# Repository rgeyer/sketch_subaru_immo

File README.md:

# Sketch Subaru IMMO
Assets for PCBs, and arduino sketch(es) relating to hacking my 2005 Subaru Outback XT engine computer.

## EAGLE
The `eagle` directory contains the PCBs. Including the following.

1. `immo_programmer` - A (reasonbly mature) immobilizer EEPROM programming tool.
2. `Bench` - A PCB which is designed to allow bench testing of the ECU/BIU/CM, which breaks out key signals (CANbus, IMMO serial, security light, etc), and includes a Teensy 3.5/3.6 for reading and manipulating singnals.
3. `ArduinoLogger` - A VERY incomplete prototype for logging CANbus, SSM, and immobilizer signals. Meant as a one-stop-shop for all data logging. Still needs lots of work.

## Sketches
There is really only one sketch, which is in the root of the repo currently. It's the arduino firmware for the `immo_programmer` board. It is meant to be interfaced by the [93l56r-cli](https://github.com/rgeyer/93l56r-cli/) golang app to read/write the EEPROMs related to the immobilizer system.

## Fritzing diagrams
The `fritzing` directory includes visual diagrams for the wiring schematics on breadboards, for those who may not be using my manufactured PCB.

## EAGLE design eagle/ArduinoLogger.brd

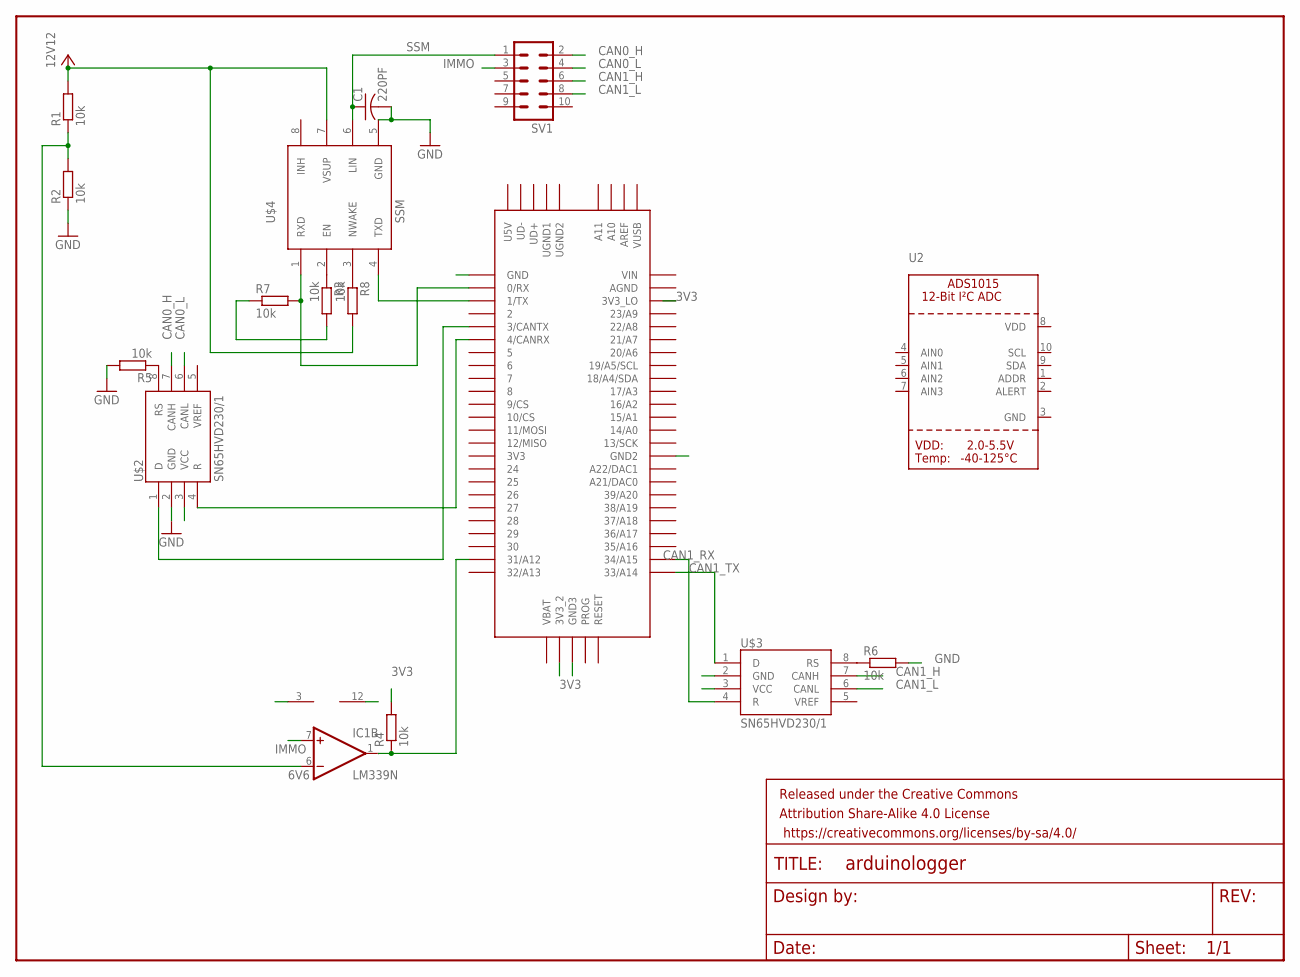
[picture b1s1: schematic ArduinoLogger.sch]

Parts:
C1: 220PF; C050-024X044
FRAME1: FRAME-LETTER; CREATIVE_COMMONS
IC1: LM339N; DIL14
R1, R2, R3, R4, R5, R6, R7, R8: 10k; 0204/7
SV1: MA05-2
U2: ADC_ADS1015; MSOP10
U$1: TEENSY_3.5/3.6
U$2, U$3: SN65HVD230/1; SO8
U$4: SSM; SOIC8

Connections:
3V3: R3.2, R4.2, R7.1, U$1.3V3_2, U$1.3V3_LO, U$2.3 (VCC), U$3.3 (VCC)
6V6: IC1.6 (-IN), R1.1, R2.2
+12V: IC1.3 (V+), R1.2, R8.2, U$4.7 (VSUP)
CAN0_H: SV1.2, U$2.7 (CANH)
CAN0_L: SV1.4, U$2.6 (CANL)
CAN1_H: SV1.6, U$3.7 (CANH)
CAN1_L: SV1.8, U$3.6 (CANL)
CAN1_RX: U$1.34/A15, U$3.4 (R)
CAN1_TX: U$1.33/A14, U$3.1 (D)
GND: C1.2, IC1.12 (GND), R2.1, R5.2, R6.2, U$1.GND, U$1.GND2, U$1.GND3, U$2.2 (GND), U$3.2 (GND), U$4.5 (GND)
IMMO: IC1.7 (+IN), SV1.3
unnamed: U$1.3/CANTX, U$2.1 (D)
unnamed: IC1.1 (OUT), R4.1, U$1.31/A12
unnamed: R7.2, U$1.0/RX, U$4.1 (RXD)
unnamed: R3.1, U$4.2 (EN)
unnamed: R8.1, U$4.3 (NWAKE)
unnamed: U$1.4/CANRX, U$2.4 (R)
unnamed: R5.1, U$2.8 (RS)
unnamed: R6.1, U$3.8 (RS)
unnamed: U$1.1/TX, U$4.4 (TXD)
SSM: C1.1, SV1.1, U$4.6 (LIN)

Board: 2 copper layers, 17 parts (0 on the bottom side), 21 nets, no tracks yet.

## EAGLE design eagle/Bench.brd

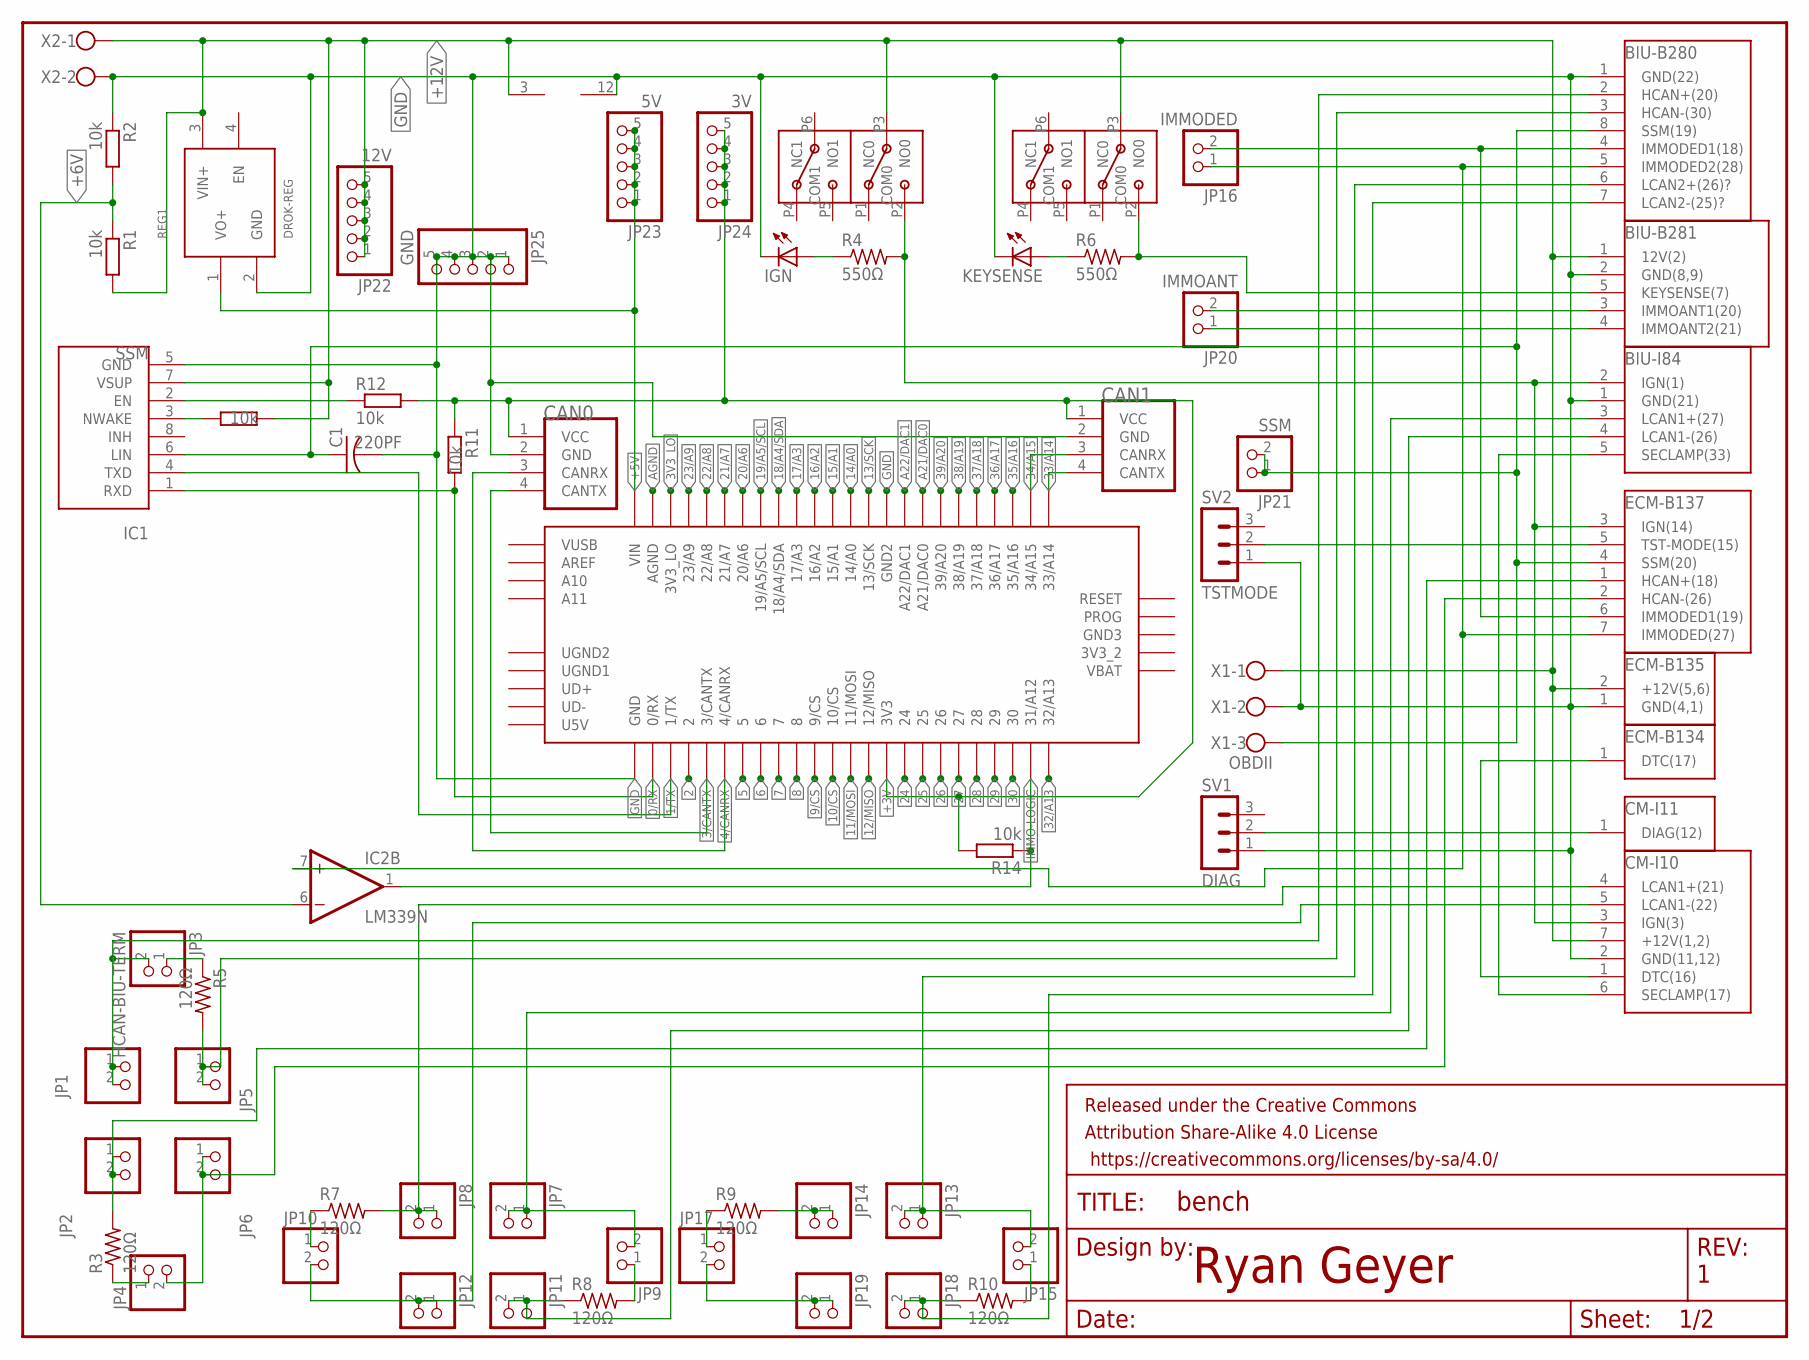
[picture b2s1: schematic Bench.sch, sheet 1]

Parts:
C1: 220PF; C050-024X044
CAN0, CAN1: SN65HVD230D-BREAKOUT; 1X04
CONN1: CM-110
CONN2: CM-I11; ECM-B134
CONN3: BIU-B280
CONN4: BIU-B281
CONN5: BIU-I84
CONN6: ECM-B135
CONN7: ECM-B137
CONN8: ECM-B134
FRAME1: FRAME-LETTER; CREATIVE_COMMONS
IC1: SSM; DIL8
IC2: LM339N; DIL14
IGN: LED3MM
JP1, JP2, JP4, JP5, JP6, JP7, JP8, JP9, JP10, JP11, JP12, JP13, JP14, JP15, JP17, JP18, JP19: PINHD-1X2; 1X02
JP3: HCAN-BIU-TERM; 1X02
JP16: IMMODED; 1X02
JP20: IMMOANT; 1X02
JP21: SSM; 1X02
JP22: 12V; 1X05
JP23: 5V; 1X05
JP24: 3V; 1X05
JP25: GND; 1X05
KEYSENSE: LED3MM
MCU1: TEENSY_3.5/3.6
R1, R2, R11, R12, R13, R14: 10k; 0207/10
R3, R5, R7, R8, R9, R10: 120Ω; 0207/10
R4, R6: 550Ω; 0207/10
REG1: DROK-REG
SV1: DIAG; MA03-1
SV2: TSTMODE; MA03-1
SW1, SW2: 8MM-DPDT
X1: OBDII; W237-103
X2: GND; W237-102

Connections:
0/RX: IC1.1 (RXD), MCU1.0/RX, R11.2; also elsewhere on the board
1/TX: IC1.4 (TXD), MCU1.1/TX; also elsewhere on the board
2: MCU1.2; also elsewhere on the board
3/CANTX: CAN0.4 (CANTX), MCU1.3/CANTX; also elsewhere on the board
3V3_LO: MCU1.3V3_LO; also elsewhere on the board
4/CANRX: CAN0.3 (CANRX), MCU1.4/CANRX; also elsewhere on the board
5: MCU1.5; also elsewhere on the board
6: MCU1.6; also elsewhere on the board
7: MCU1.7; also elsewhere on the board
8: MCU1.8; also elsewhere on the board
9/CS: MCU1.9/CS; also elsewhere on the board
10/CS: MCU1.10/CS; also elsewhere on the board
11/MOSI: MCU1.11/MOSI; also elsewhere on the board
12/MISO: MCU1.12/MISO; also elsewhere on the board
13/SCK: MCU1.13/SCK; also elsewhere on the board
14/A0: MCU1.14/A0; also elsewhere on the board
15/A1: MCU1.15/A1; also elsewhere on the board
16/A2: MCU1.16/A2; also elsewhere on the board
17/A3: MCU1.17/A3; also elsewhere on the board
18/A4/SDA: MCU1.18/A4/SDA; also elsewhere on the board
19/A5/SCL: MCU1.19/A5/SCL; also elsewhere on the board
20/A6: MCU1.20/A6; also elsewhere on the board
21/A7: MCU1.21/A7; also elsewhere on the board
22/A8: MCU1.22/A8; also elsewhere on the board
23/A9: MCU1.23/A9; also elsewhere on the board
24: MCU1.24; also elsewhere on the board
25: MCU1.25; also elsewhere on the board
26: MCU1.26; also elsewhere on the board
27: MCU1.27; also elsewhere on the board
28: MCU1.28; also elsewhere on the board
29: MCU1.29; also elsewhere on the board
30: MCU1.30; also elsewhere on the board
32/A13: MCU1.32/A13; also elsewhere on the board
33/A14: CAN1.4 (CANTX), MCU1.33/A14; also elsewhere on the board
34/A15: CAN1.3 (CANRX), MCU1.34/A15; also elsewhere on the board
35/A16: MCU1.35/A16; also elsewhere on the board
36/A17: MCU1.36/A17; also elsewhere on the board
37/A18: MCU1.37/A18; also elsewhere on the board
38/A19: MCU1.38/A19; also elsewhere on the board
39/A20: MCU1.39/A20; also elsewhere on the board
+3V: CAN0.1 (VCC), CAN1.1 (VCC), JP24.1, JP24.2, JP24.3, JP24.4, JP24.5, MCU1.3V3, R11.1, R12.2, R14.2; also elsewhere on the board
+5V: JP23.1, JP23.2, JP23.3, JP23.4, JP23.5, MCU1.VIN, REG1.1 (VO+); also elsewhere on the board
+6V: IC2.6 (-IN), R1.1, R2.2
+12V: CONN1.7 (+12V(1,2)), CONN4.1 (12V(2)), CONN6.2 (+12V(5,6)), IC1.7 (VSUP), IC2.3 (V+), JP22.1, JP22.2, JP22.3, JP22.4, JP22.5, R1.2, R13.2, REG1.3 (VIN+), SW1.P3 (COM0), SW2.P3 (COM0), X1.1, X2.1
A21/DAC0: MCU1.21/DAC0 (A21/DAC0); also elsewhere on the board
A22/DAC1: MCU1.A22/DAC1; also elsewhere on the board
AGND: MCU1.AGND; also elsewhere on the board
GND: C1.2, CAN0.2 (GND), CAN1.2 (GND), CONN1.2 (GND(11,12)), CONN3.1 (GND(22)), CONN4.2 (GND(8,9)), CONN5.1 (GND(21)), CONN6.1 (GND(4,1)), IC1.5 (GND), IC2.12 (GND), IGN.K (C), JP25.1, JP25.2, JP25.3, JP25.4, JP25.5, KEYSENSE.K (C), MCU1.GND, MCU1.GND2, R2.1, REG1.2 (GND), SV1.1, SV2.1, X1.2, X2.2; also elsewhere on the board
HCAN+(BIU): CONN3.2 (HCAN+(20)), JP1.1, JP1.2, JP3.2
HCAN+(ECM): CONN7.1 (HCAN+(18)), JP2.1, JP2.2, R3.2
HCAN-(BIU): CONN3.3 (HCAN-(30)), JP5.1, JP5.2, R5.2
HCAN-(ECM): CONN7.2 (HCAN-(26)), JP4.2, JP6.1, JP6.2
IGN: CONN1.3 (IGN(3)), CONN5.2 (IGN(1)), CONN7.3 (IGN(14)), R4.2, SW1.P2 (NO0)
IMMO-LOGIC: IC2.1 (OUT), MCU1.31/A12, R14.1; also elsewhere on the board
KEYSENSE: CONN4.5 (KEYSENSE(7)), R6.2, SW2.P2 (NO0)
LCAN1+(BIU): CONN5.3 (LCAN1+(27)), JP7.1, JP7.2, JP9.2
LCAN1+(CM): CONN1.4 (LCAN1+(21)), JP8.1, JP8.2, R7.2
LCAN1-(BIU): CONN5.4 (LCAN1-(26)), JP11.1, JP11.2, R8.1
LCAN1-(CM): CONN1.5 (LCAN1-(22)), JP10.2, JP12.1, JP12.2
LCAN2+(BIU): CONN3.6 (LCAN2+(26)?), JP13.1, JP13.2, JP15.2
LCAN2+(CLI): JP14.1, JP14.2, R9.2
LCAN2-(BIU): CONN3.7 (LCAN2-(25)?), JP18.1, JP18.2, R10.1
LCAN2-(CLI): JP17.2, JP19.1, JP19.2
unnamed: IGN.A, R4.1
unnamed: CONN1.6 (SECLAMP(17)), CONN5.5 (SECLAMP(33))
unnamed: KEYSENSE.A, R6.1
unnamed: CONN1.1 (DTC(16)), CONN8.1
unnamed: CONN2.1, SV1.2
unnamed: JP9.1, R8.2
unnamed: JP3.1, R5.1
unnamed: JP4.1, R3.1
unnamed: JP10.1, R7.1
unnamed: JP15.1, R10.2
unnamed: IC1.2 (EN), R12.1
unnamed: IC1.3 (NWAKE), R13.1
unnamed: JP17.1, R9.1
unnamed: CONN3.4 (IMMODED1(18)), CONN7.6 (IMMODED1(19)), JP16.2
unnamed: CONN3.5 (IMMODED2(28)), CONN7.7 (IMMODED(27)), IC2.7 (+IN), JP16.1
unnamed: CONN4.3 (IMMOANT1(20)), JP20.2
unnamed: CONN4.4 (IMMOANT2(21)), JP20.1
SSM: C1.1, CONN3.8 (SSM(19)), CONN7.4 (SSM(20)), IC1.6 (LIN), JP21.1, JP21.2, X1.3
TSTMODE: CONN7.5 (TST-MODE(15)), SV2.2

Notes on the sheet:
Ryan Geyer

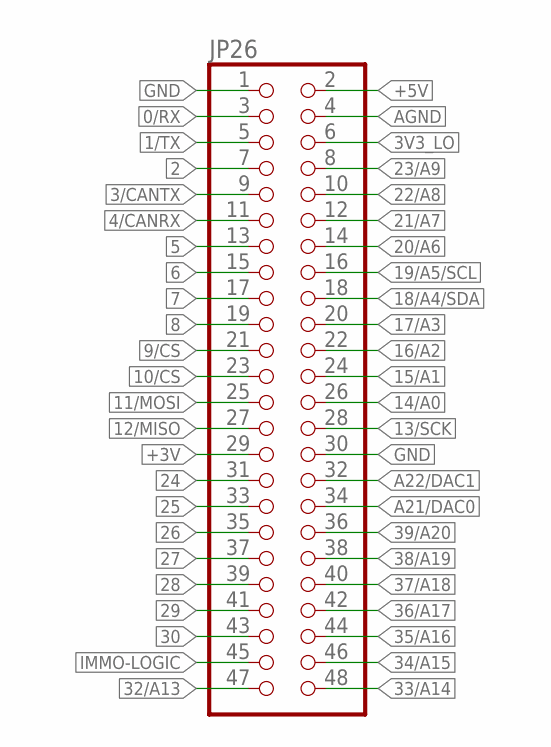
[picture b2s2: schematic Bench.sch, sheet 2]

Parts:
JP26: PINHD-2X24; 2X24

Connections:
0/RX: JP26.3; also elsewhere on the board
1/TX: JP26.5; also elsewhere on the board
2: JP26.7; also elsewhere on the board
3/CANTX: JP26.9; also elsewhere on the board
3V3_LO: JP26.6; also elsewhere on the board
4/CANRX: JP26.11; also elsewhere on the board
5: JP26.13; also elsewhere on the board
6: JP26.15; also elsewhere on the board
7: JP26.17; also elsewhere on the board
8: JP26.19; also elsewhere on the board
9/CS: JP26.21; also elsewhere on the board
10/CS: JP26.23; also elsewhere on the board
11/MOSI: JP26.25; also elsewhere on the board
12/MISO: JP26.27; also elsewhere on the board
13/SCK: JP26.28; also elsewhere on the board
14/A0: JP26.26; also elsewhere on the board
15/A1: JP26.24; also elsewhere on the board
16/A2: JP26.22; also elsewhere on the board
17/A3: JP26.20; also elsewhere on the board
18/A4/SDA: JP26.18; also elsewhere on the board
19/A5/SCL: JP26.16; also elsewhere on the board
20/A6: JP26.14; also elsewhere on the board
21/A7: JP26.12; also elsewhere on the board
22/A8: JP26.10; also elsewhere on the board
23/A9: JP26.8; also elsewhere on the board
24: JP26.31; also elsewhere on the board
25: JP26.33; also elsewhere on the board
26: JP26.35; also elsewhere on the board
27: JP26.37; also elsewhere on the board
28: JP26.39; also elsewhere on the board
29: JP26.41; also elsewhere on the board
30: JP26.43; also elsewhere on the board
32/A13: JP26.47; also elsewhere on the board
33/A14: JP26.48; also elsewhere on the board
34/A15: JP26.46; also elsewhere on the board
35/A16: JP26.44; also elsewhere on the board
36/A17: JP26.42; also elsewhere on the board
37/A18: JP26.40; also elsewhere on the board
38/A19: JP26.38; also elsewhere on the board
39/A20: JP26.36; also elsewhere on the board
+3V: JP26.29; also elsewhere on the board
+5V: JP26.2; also elsewhere on the board
A21/DAC0: JP26.34; also elsewhere on the board
A22/DAC1: JP26.32; also elsewhere on the board
AGND: JP26.4; also elsewhere on the board
GND: JP26.1, JP26.30; also elsewhere on the board
IMMO-LOGIC: JP26.45; also elsewhere on the board

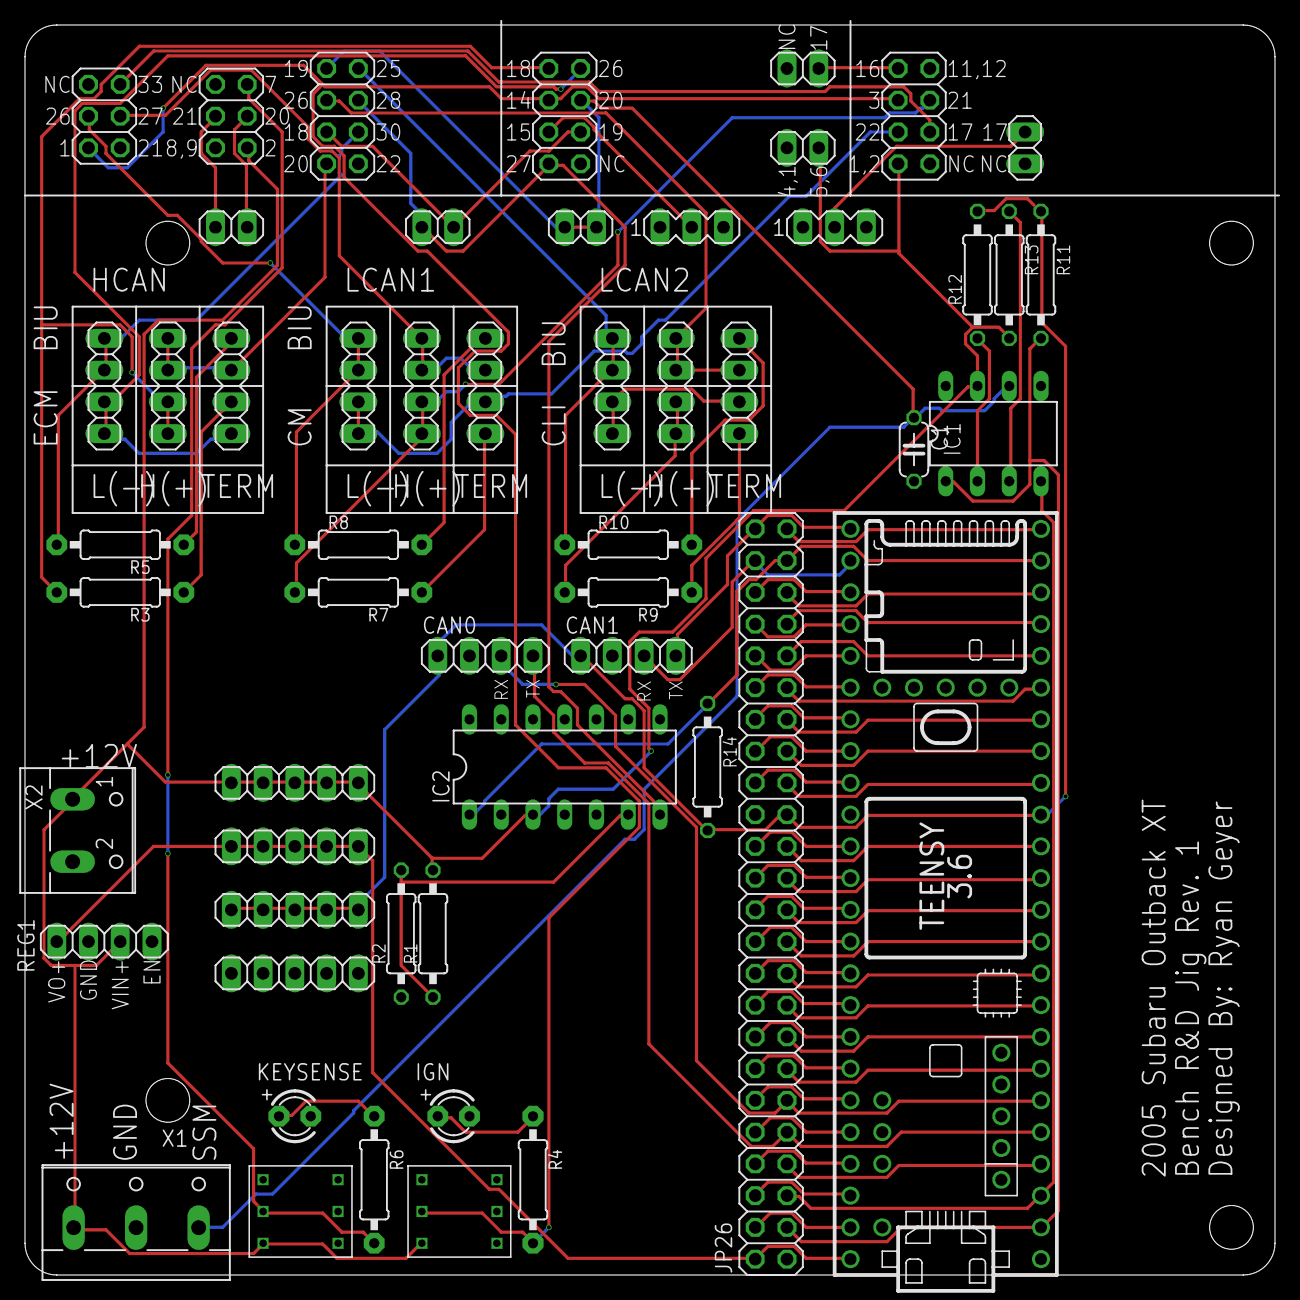
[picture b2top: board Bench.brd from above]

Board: 2 copper layers, 100.0 x 100.0 mm, 64 parts (0 on the bottom side), 82 nets.

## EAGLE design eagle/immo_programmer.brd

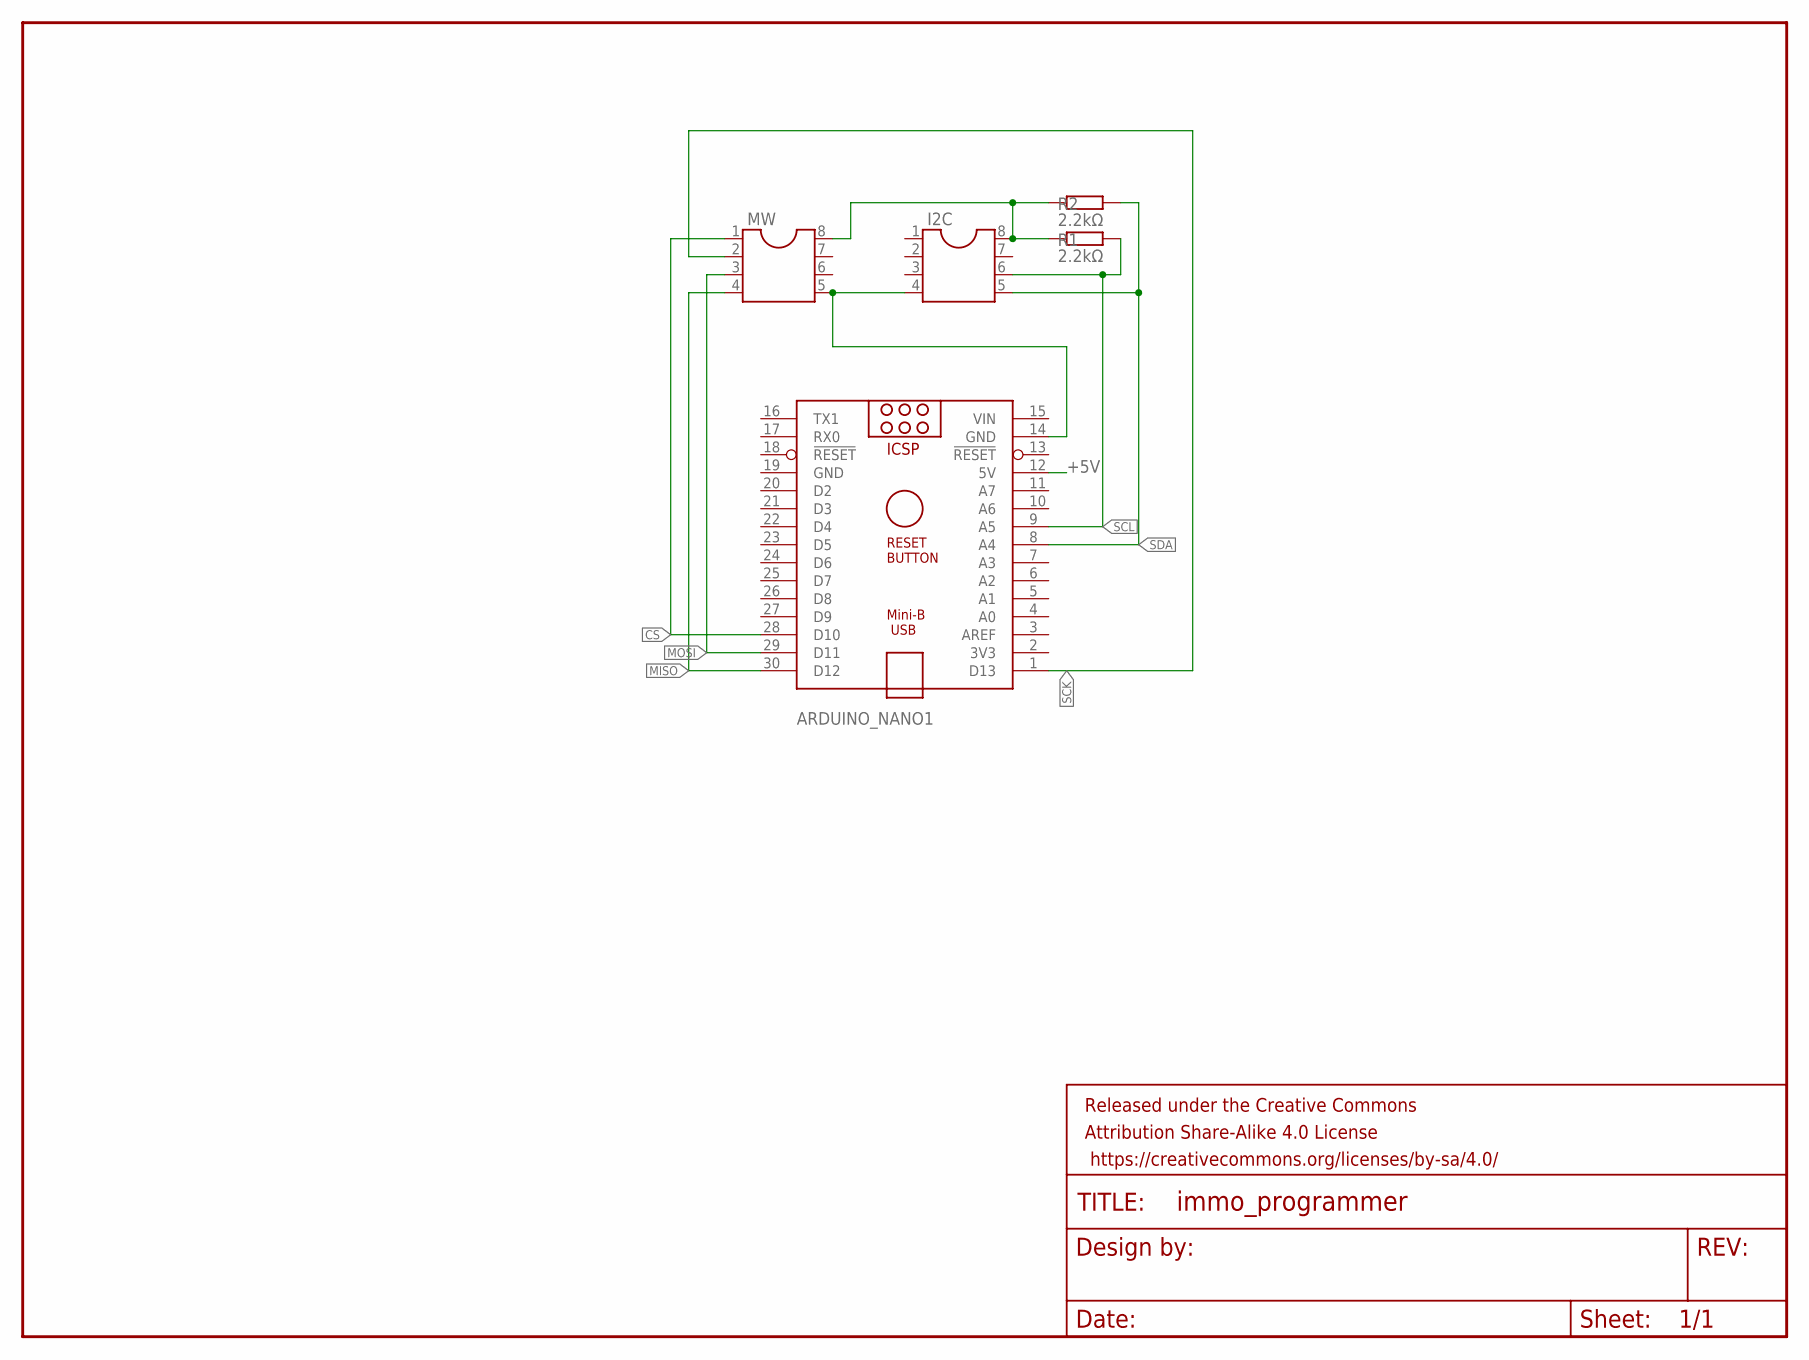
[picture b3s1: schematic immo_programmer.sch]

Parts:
ARDUINO_NANO1: ARDUINO_NANO
FRAME1: FRAME-LETTER; CREATIVE_COMMONS
I2C: DIL8; DIL08
MW: DIL8; DIL08
R1, R2: 2.2kΩ; 0207/10

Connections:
+5V: ARDUINO_NANO1.12 (5V), I2C.8, MW.8, R1.1, R2.1
CS: ARDUINO_NANO1.28 (D10), MW.1
GND: ARDUINO_NANO1.14 (GND), ARDUINO_NANO1.19 (GND), I2C.4, MW.5
MISO: ARDUINO_NANO1.30 (D12), MW.4
MOSI: ARDUINO_NANO1.29 (D11), MW.3
SCK: ARDUINO_NANO1.1 (D13), MW.2
SCL: ARDUINO_NANO1.9 (A5), I2C.6, R1.2
SDA: ARDUINO_NANO1.8 (A4), I2C.5, R2.2
VIN: ARDUINO_NANO1.15 (VIN)

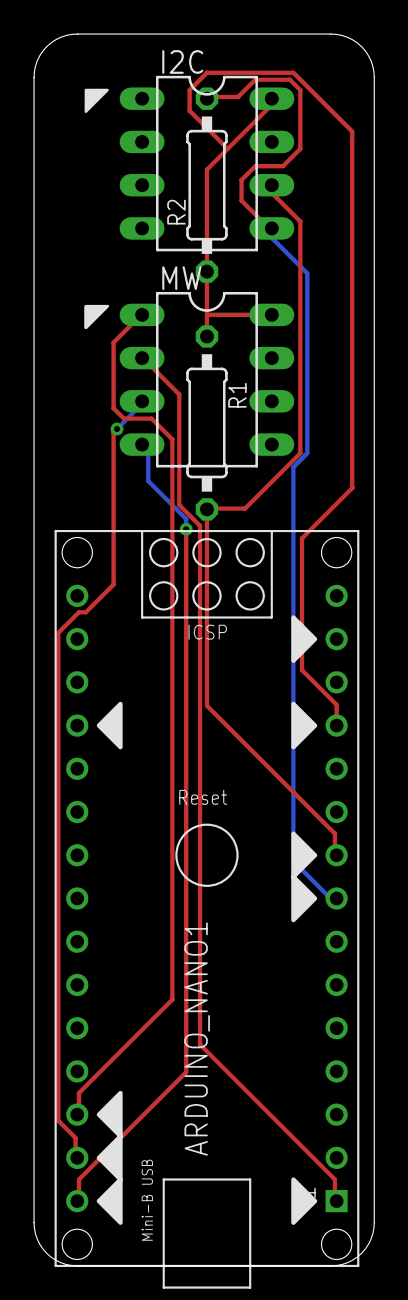
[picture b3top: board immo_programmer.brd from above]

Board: 2 copper layers, 20.0 x 72.4 mm, 6 parts (0 on the bottom side), 8 nets.

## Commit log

2018-11-23 Initial Commit, read working, beginning efforts for write
2019-01-06 Finished write, with proper blocking and timing
2019-01-06 Remove unused pin variable
2019-01-06 Add fritzing sketches
2019-01-19 Added support for Teensy 2.0, which does not reset on Serial Monitor connection
2019-02-04 minor todos
2019-02-05 Blink LEDs, and distinguish between boards better
2019-02-20 Switch to COBS packets for serial communication. Remove fixed size in-memory buffer for EEPROM contents
2019-02-22 MW writes in chunks delivered by COBS packets. Added I2C read
2019-02-23 Implement I2C write
2019-03-17 Add full Arduino Nano fritzing diagram
2019-10-08 Switch to platform.io for multi platform compilation
2023-12-30 Add eagle pcb files
2023-12-30 Add labels to more nets

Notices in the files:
parts and their libraries:
SparkFun-Aesthetics: Licensing: Creative Commons ShareAlike 4.0 International - https://creativecommons.org/licenses/by-sa/4.0
SparkFun-Aesthetics: Released under the Creative Commons Attribution Share-Alike 4.0 License
SparkFun-Aesthetics: https://creativecommons.org/licenses/by-sa/4.0
